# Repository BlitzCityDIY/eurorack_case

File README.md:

# eurorack_case

This is a Eurorack case that I designed with Noe Ruiz. It's a 6U 84HP case. All files are provided so that you can build your own or modify.

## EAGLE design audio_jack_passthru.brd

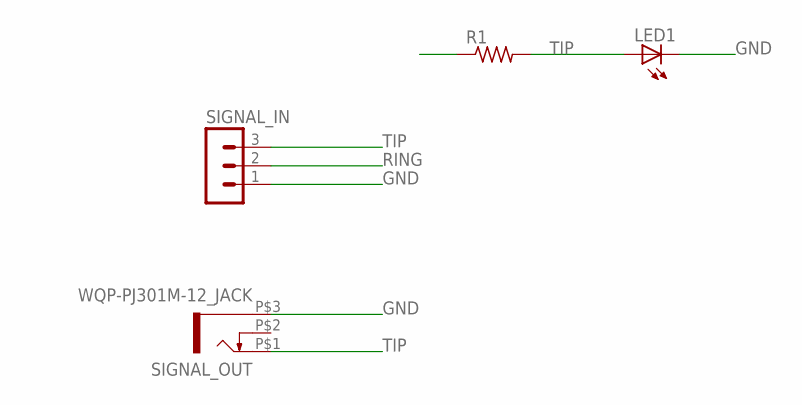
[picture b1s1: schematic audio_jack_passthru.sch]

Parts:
LED1: LED3MM
R1: R-US_R0805; R0805
SIGNAL_IN: MA03-1
SIGNAL_OUT: WQP-PJ301M-12_JACK

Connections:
GND: LED1.K (C), SIGNAL_IN.1, SIGNAL_OUT.P$3 (1)
RING: SIGNAL_IN.2
TIP: LED1.A, R1.1, R1.2, SIGNAL_IN.3, SIGNAL_OUT.P$1 (2)

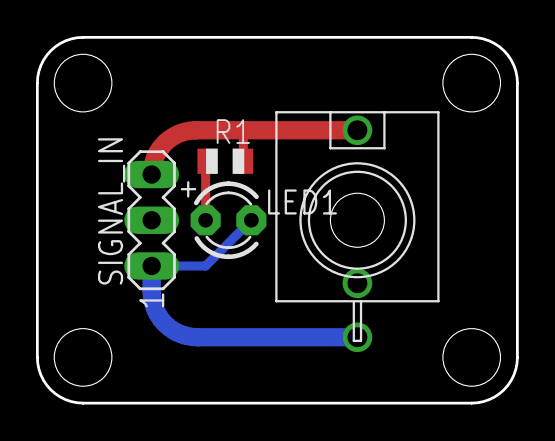
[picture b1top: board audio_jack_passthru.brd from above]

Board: 2 copper layers, 26.7 x 20.3 mm, 8 parts (1 on the bottom side), 2 nets.

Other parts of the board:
PLABEL0: PLABEL0
PLABEL1: PLABEL1
PLABEL2: PLABEL2
PLABEL3: PLABEL3

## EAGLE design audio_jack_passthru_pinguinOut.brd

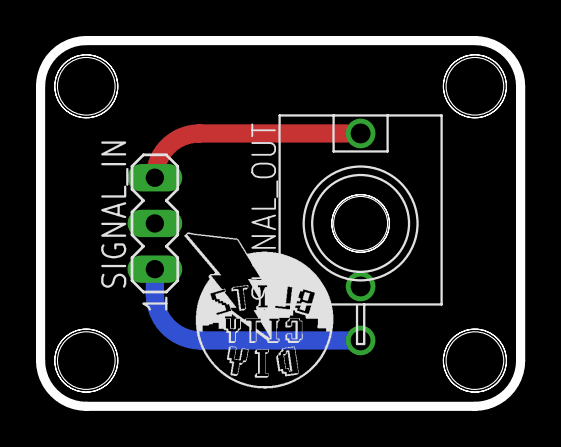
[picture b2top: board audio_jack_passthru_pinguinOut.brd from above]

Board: 2 copper layers, 26.7 x 20.3 mm, 6 parts (1 on the bottom side), 2 nets.

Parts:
SIGNAL_IN: MA03-1
SIGNAL_OUT: WQP-PJ301M-12_JACK
pLabel0: pLabel0
pLabel1: pLabel1
pLabel2: pLabel2
pLabel3: pLabel3

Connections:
GND: SIGNAL_IN.1, SIGNAL_OUT.P$3
TIP: SIGNAL_IN.3, SIGNAL_OUT.P$1

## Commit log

2021-02-19 Adding svg, stl, dxf, step and f3d
    Adding stl, svg and dxf of the side panel and acrylic panel. Also adding step and f3d of entire project.
2021-02-19 Update README.md
    adding description
2021-02-19 Adding files for tip top z rails
    Adding files for tip top z rails
2024-05-27 keystep patch bay PCB files
2024-05-27 patchbay CAD
